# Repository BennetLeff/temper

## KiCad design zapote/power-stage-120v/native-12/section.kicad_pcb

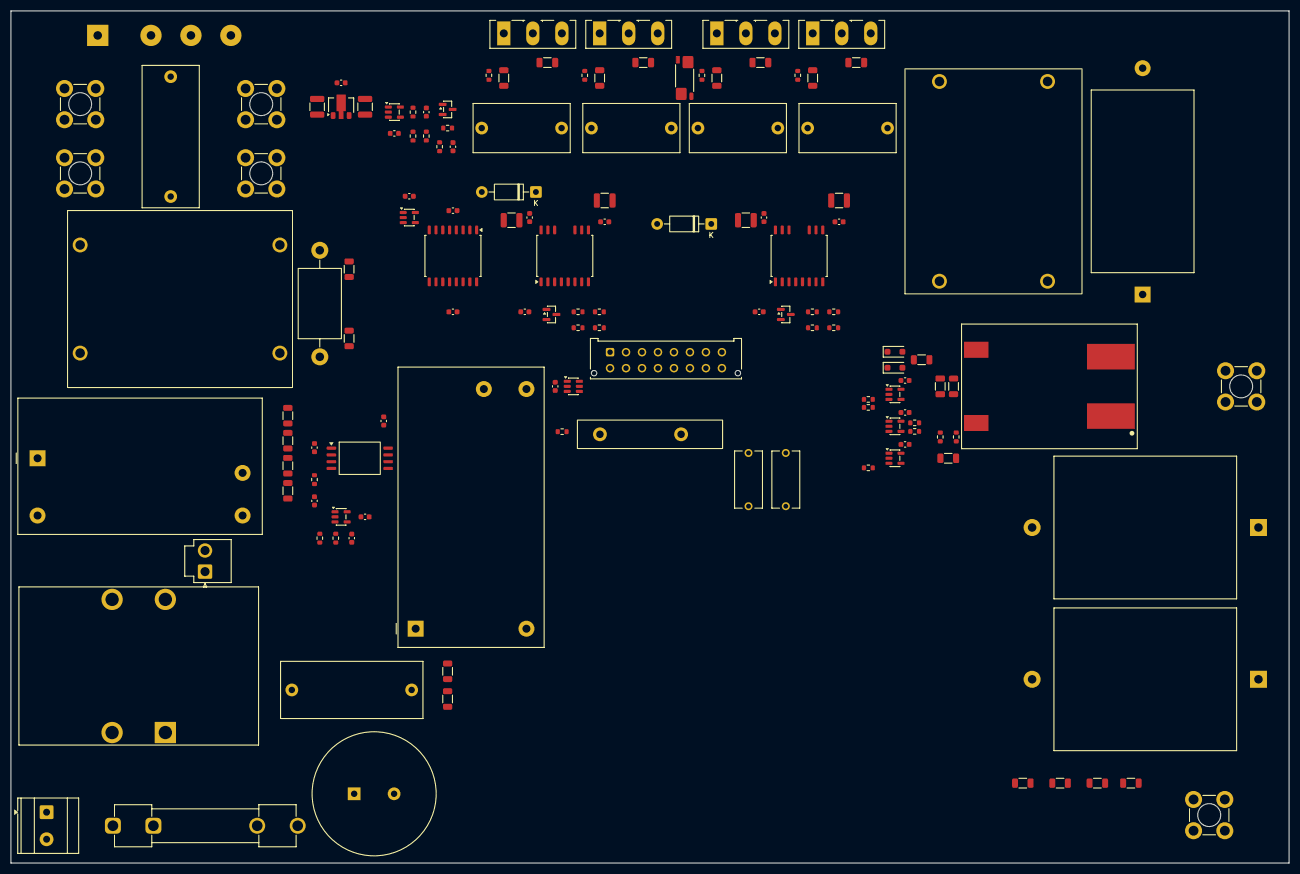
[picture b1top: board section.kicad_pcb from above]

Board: 4 copper layers, 240.0 x 160.0 mm, 135 parts (0 on the bottom side), 72 nets, no tracks yet.

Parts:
BR1: GBJ2510-F; Diode_Bridge_GBJ2510
C1, C2: R463R410000M1M; C_Rect_L26.5mm_W10.5mm_P22.50mm_MKS4
C3, C4: DE1E3RA222MA4BP01F; Murata_DE1E3RA222MA4BP01F_P10.0_Pad1.5_ReviewOnly
C5, C6: B32656G0275J000; TDK_B32656G0275J000_4Pin_P37.50_P20.30_ReviewOnly
C7, C8, C11, C14, C15, C18, C25, C28, C29, C32, C34, C35, C36, C37, C44, C45, C46, C47: C0603C104K5RACTU; C_0603_1608Metric
C9, C10, C16, C17, C24, C26: GRM32ER71H106KA12L; C_1210_3225Metric
C12, C13, C19, C20: GRM31A5C3A102JW01D; C_1206_3216Metric
C21, C22: 942C12P22K-F; CDE_942C_D26.5_L34.0_Axial_ReviewOnly
C23: 942C12P1K-F; CDE_942C_D19.0_L34.0_Axial_ReviewOnly
C27, C31, C33: C0603C102J5GACTU; C_0603_1608Metric
C30: C0603C101J5GACTU; C_0603_1608Metric
C38, C39, C40, C41: B32652A0104K000; TDK_B32652A0104K000_P15.00_ReviewOnly
C42, C43: GRM31C5C1H104JA01L; C_1206_3216Metric
D1, D2: UF4007-E3/54; D_DO-41_SOD81_P10.16mm_Horizontal
D3: MRT130KP295CV; MRT130KP_Axial_P20.00mm_ReviewOnly
D4, D5: BAS116H,115; D_SOD-123F
F1: 0326020.MXP; Fuseholder_Clip-6.3x32mm_Littelfuse_102071_Inline_P34.70x7.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
J1: 1711725; TerminalBlock_Phoenix_MKDS-3-2-5.08_1x02_P5.08mm_Horizontal
J2, J5, J7, J8, J9, J10: 74650074; Wuerth_REDCUBE-THR_WP-THRBU_74650074_THR
J3: B2P-VH(LF)(SN); JST_VH_B2P-VH_1x02_P3.96mm_Vertical
J4: 0430451612; Molex_Micro-Fit_3.0_43045-1612_2x08_P3.00mm_Vertical
J6: 1704004; Phoenix_KDS3_1704004_1Pos_2Pin_ReviewOnly
L1: B82726S2203A020; B82726S2_ReviewOnly
PS1: IRM-20-15; Converter_ACDC_MeanWell_IRM-20-xx_THT
PS2: IRM-05-15; Converter_ACDC_MeanWell_IRM-05-xx_THT
Q1, Q4: AO3400A; SOT-23
Q2, Q3, Q5, Q6: IPW65R018CFD7; TO-247-3_Vertical
R1, R2: RC1206FR-07120KL; R_1206_3216Metric
R3, R4: RC1206FR-07220KL; R_1206_3216Metric
R5: WSK2512R0010FEA; R_Shunt_Vishay_WSK2512_6332Metric_T1.19mm
R6, R14: RC0603FR-07100RL; R_0603_1608Metric
R7, R15: RC0603FR-07100KL; R_0603_1608Metric
R8, R16, R47: RC0603FR-071KL; R_0603_1608Metric
R9, R17: RC0603FR-0739KL; R_0603_1608Metric
R10, R12, R18, R20: RC1206FR-073R9L; R_1206_3216Metric
R11, R13, R19, R21: RC0603FR-0710KL; R_0603_1608Metric
R22, R23, R24, R25, R26, R27, R28, R29: RC1206FR-07470KL; R_1206_3216Metric
R30: RT0603BRD0715K8L; R_0603_1608Metric
R31: RC0603FR-075K6L; R_0603_1608Metric
R32, R33, R35, R36, R44, R45: RT0603BRD0710KL; R_0603_1608Metric
R34: RT0603BRD0710K5L; R_0603_1608Metric
R37: RT0603BRD07140KL; R_0603_1608Metric
R38: RC0603JR-070RL; R_0603_1608Metric
R39: RC1206FR-071R5L; R_1206_3216Metric
R40, R41: RT0603BRD071KL; R_0603_1608Metric
R42: RC1206FR-071KL; R_1206_3216Metric
R43, R46: RT0603BRD073K32L; R_0603_1608Metric
RV1: TMOV20RP175E; TMOV20RP_ReviewOnly
T1: CST3015-100ED; CST3015
U1, U2: UCC21550BDWKR; SOIC16W_Isolated
U3: MC78L05ACHT1G; SOT-89-3
U4: AMC1311BDWVR; SOIC-8_7.5x5.85mm_P1.27mm
U5: LM4040A25IDBZR; SOT-23
U6, U7, U10, U11, U12: TLV3201AIDBVR; SOT-23-5
U8: SN74LVC1G00DBVR; SOT-23-5
U9: ISO7710DWR; SOIC16W_DW0016B_HV
U13: SN74LVC1G332DBVR; SOT-23-6

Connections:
ac_l_in: F1.1, J1.1
ac_n_in: C1.2, J1.2, L1.2, R2.2, RV1.2
bus_fault: J4.10, U13.4
bus_fault_hot: U8.4, U9.4
bus_fault_iso: U9.13, U13.1
bus_p: C5.1, C5.2, C6.1, C6.2, C12.1, C19.1, C38.1, C39.1, C40.1, C41.1, D3.1, J8.1, Q2.2, Q5.2, R3.1, R26.1
busbleed_mid: R3.2, R4.1
coil_feed: J2.1, T1.2
crbleed_1: R22.2, R23.1
crbleed_2: R23.2, R24.1
crbleed_3: R24.2, R25.1
ct_mon: J4.14, R47.2
ct_oc_neg: U11.1, U13.6
ct_oc_pos: U10.1, U13.3
ct_ref_hi: R43.2, R44.1, U10.4
ct_ref_lo: R45.2, R46.1, U11.3
ct_s1: C42.1, R39.1, R42.1, T1.3
ct_s2: C42.2, C43.1, R39.2, R40.2, R41.1, T1.4, U12.4
ct_sense_mon: D4.2, D5.1, R42.2, R47.1, U10.3, U11.4, U12.3
ct_zc: J4.13, U12.1
hot5: C26.1, C28.1, C32.1, C34.1, C35.1, C36.1, R31.1, U3.1, U4.1, U6.5, U7.5, U8.5, U9.3
hv_ret: C5.3, C5.4, C6.3, C6.4, C38.2, C39.2, C40.2, C41.2, D3.2, J10.1, R4.2, R5.4
l_f: C1.1, F1.2, L1.1, R1.1, RV1.1
l_filt: BR1.2, C2.1, C3.1, J3.1, L1.4, PS1.1
leg_a-boot: C10.1, C11.1, D1.1, U1.16
leg_a-dis: Q1.3, R8.1, U1.5
leg_a-gate_h: Q2.1, R10.2, R11.1
leg_a-gate_l: Q3.1, R12.2, R13.1
leg_a-out_h: R10.1, U1.15
leg_a-out_l: R12.1, U1.10
leg_a-permit_gate: Q1.1, R6.2, R7.1
leg_a.driver-dt: R9.1, U1.6
leg_b-boot: C17.1, C18.1, D2.1, U2.16
leg_b-dis: Q4.3, R16.1, U2.5
leg_b-gate_h: Q5.1, R18.2, R19.1
leg_b-gate_l: Q6.1, R20.2, R21.1
leg_b-out_h: R18.1, U2.15
leg_b-out_l: R20.1, U2.10
leg_b-permit_gate: Q4.1, R14.2, R15.1
leg_b.driver-dt: R17.1, U2.6
leg_ret: C8.2, C9.2, C13.2, C15.2, C16.2, C20.2, C24.2, C25.2, C26.2, C27.2, C28.2, C30.2, C31.2, C32.2, C33.2, C34.2, C35.2, C36.2, PS2.3, Q3.3, Q6.3, R5.1, R5.2, R13.2, R21.2, R30.2, R35.2, R37.2, U1.9, U2.9, U3.2, U4.3, U4.4, U5.2, U6.2, U7.2, U8.3, U9.1, U9.7
n_filt: BR1.3, C2.2, C4.1, L1.3, PS1.2, PS2.1
ocp_kelvin_n: R5.3, R33.2
ocp_node: C30.1, R32.2, R33.1, U6.3
ocp_ok_hot: U6.1, U8.1
ocp_thresh: C31.1, R34.2, R35.1, U6.4
ovp_ok_hot: U7.1, U8.2
ovp_thresh: C33.1, R36.2, R37.1, U7.3
pe: C3.2, C4.2, J6.1, J6.2, R38.1
permit: J4.9, R6.1, R14.1
pwm_ha: J4.5, U1.1
pwm_hb: J4.7, U2.1
pwm_la: J4.6, U1.2
pwm_lb: J4.8, U2.2
rect_n: BR1.4, J9.1
rect_p: BR1.1, J7.1
ref25: R31.2, R32.1, R34.1, R36.1, U5.1
res_a: C21.1, C22.1, C23.1, J5.1, R22.1
selv_gnd: C7.2, C14.2, C29.2, C37.2, C43.2, C44.2, C45.2, C46.2, C47.2, D5.2, J4.2, J4.4, J4.15, J4.16, PS1.3, Q1.2, Q4.2, R7.2, R9.2, R15.2, R17.2, R38.2, R41.2, R44.2, R46.2, U1.4, U2.4, U4.5, U9.9, U9.16, U10.2, U11.2, U12.2, U13.2
sw_a: C10.2, C11.2, C12.2, C13.1, Q2.3, Q3.2, R11.2, T1.1, U1.14
sw_b: C17.2, C18.2, C19.2, C20.1, C21.2, C22.2, C23.2, Q5.3, Q6.2, R19.2, R25.2, U2.14
tco_l: J3.2, PS2.2
v3v3: C7.1, C14.1, C29.1, C37.1, C44.1, C45.1, C46.1, C47.1, D4.1, J4.3, R8.2, R16.2, R40.1, R43.1, R45.1, U1.3, U1.8, U2.3, U2.8, U4.8, U9.14, U10.5, U11.5, U12.5, U13.5
v15_ls: C8.1, C9.1, C15.1, C16.1, C24.1, C25.1, D1.2, D2.2, PS2.4, U1.11, U2.11, U3.3
v15_selv: J4.1, PS1.4
vbus_n: J4.12, U4.6
vbus_p: J4.11, U4.7
vdiv_1: R26.2, R27.1
vdiv_2: R27.2, R28.1
vdiv_3: R28.2, R29.1
vsense_in: C27.1, R29.2, R30.1, U4.2, U7.4
xbleed_mid: R1.2, R2.1

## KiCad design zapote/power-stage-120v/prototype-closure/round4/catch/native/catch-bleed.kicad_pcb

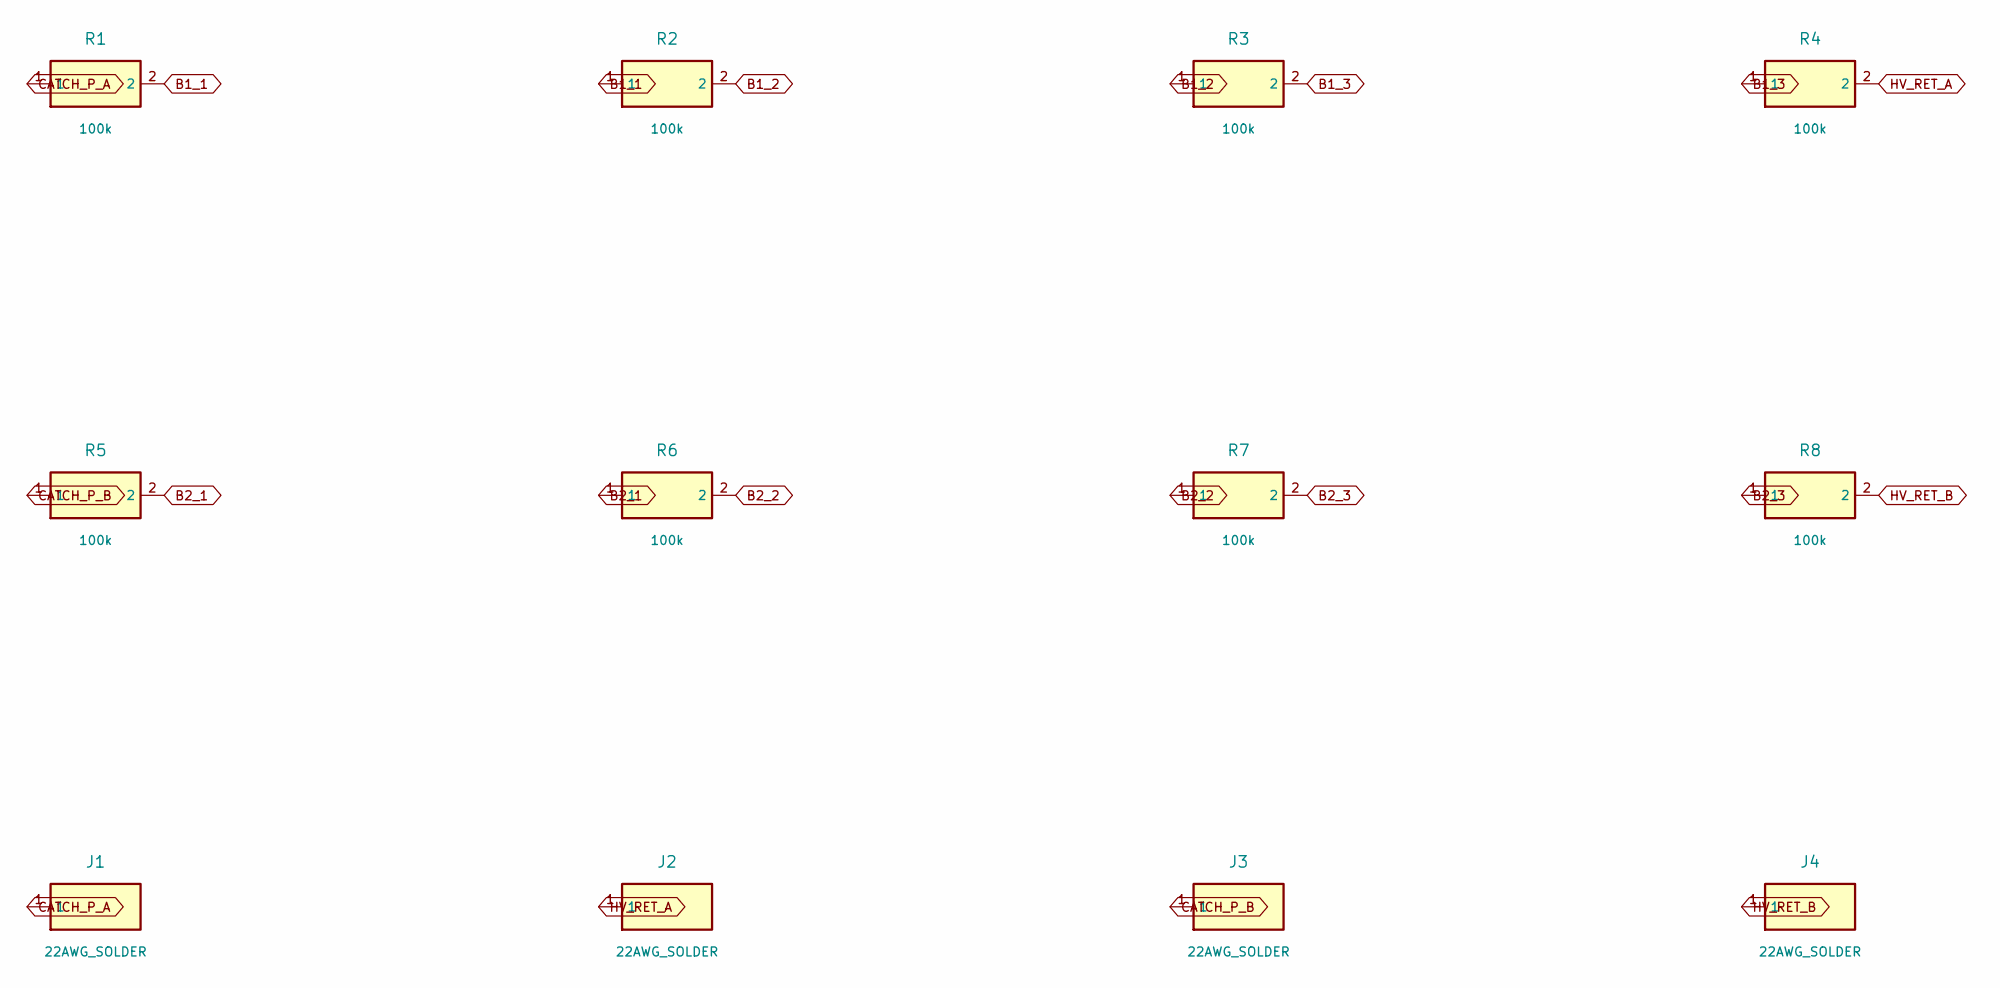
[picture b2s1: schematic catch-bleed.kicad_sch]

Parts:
J1, J2, J3, J4: 22AWG_SOLDER; WirePad
R1, R2, R3, R4, R5, R6, R7, R8: 100k; VR37_P15

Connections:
B1_1: R1.2, R2.1
B1_2: R2.2, R3.1
B1_3: R3.2, R4.1
B2_1: R5.2, R6.1
B2_2: R6.2, R7.1
B2_3: R7.2, R8.1
CATCH_P_A: J1.1, R1.1
CATCH_P_B: J3.1, R5.1
HV_RET_A: J2.1, R4.2
HV_RET_B: J4.1, R8.2

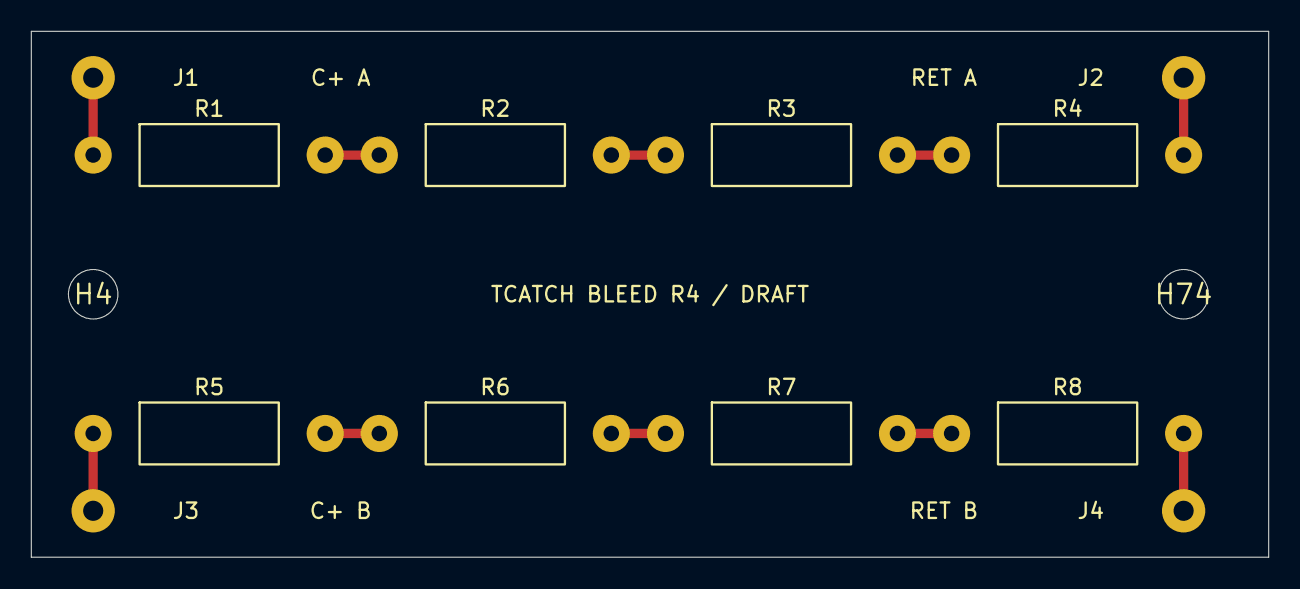
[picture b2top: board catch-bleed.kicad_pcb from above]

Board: 2 copper layers, 80.0 x 34.0 mm, 14 parts (0 on the bottom side), 10 nets.

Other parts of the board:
H4, H74: (no value)
